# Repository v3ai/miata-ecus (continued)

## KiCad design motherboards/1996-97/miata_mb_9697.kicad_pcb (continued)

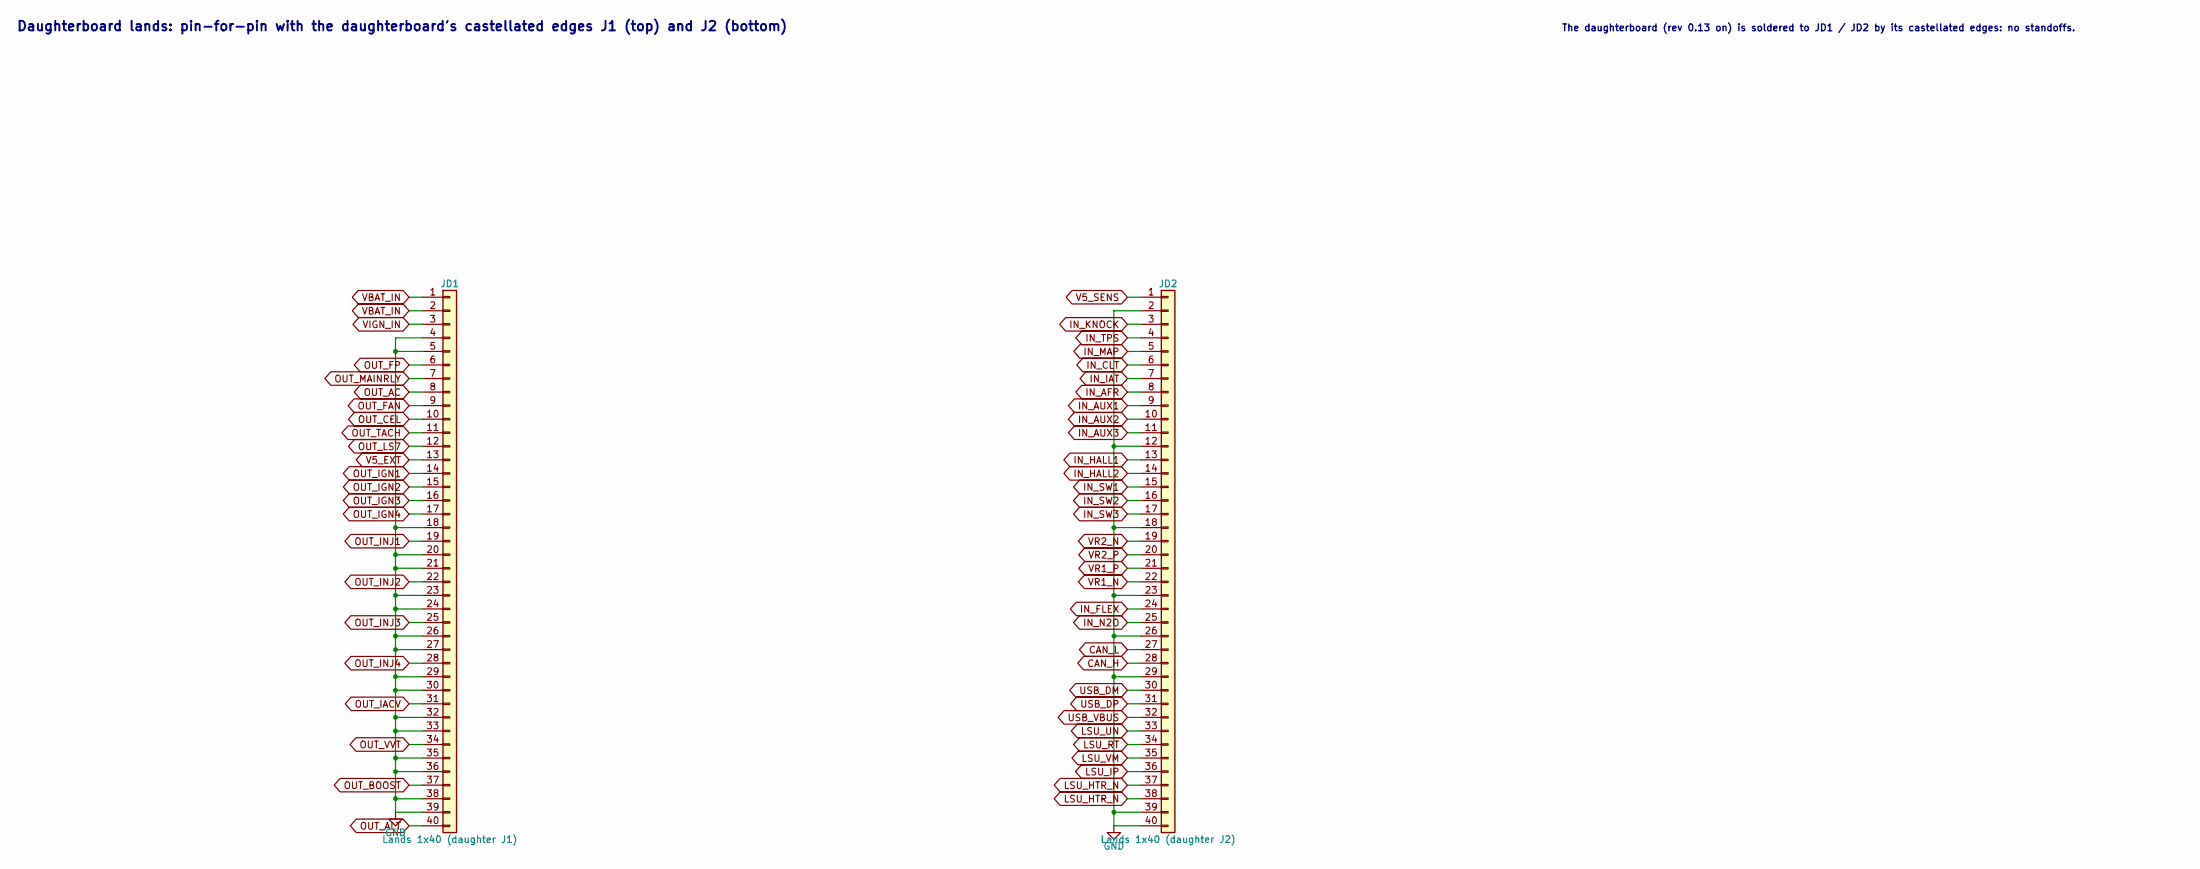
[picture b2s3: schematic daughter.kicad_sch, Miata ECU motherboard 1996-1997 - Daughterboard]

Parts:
JD1: Lands 1x40 (daughter J1); CastellatedLand_1x40_P2.54mm_TopEdge
JD2: Lands 1x40 (daughter J2); CastellatedLand_1x40_P2.54mm_BottomEdge

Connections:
CAN_H: JD2.28; also elsewhere on the board
CAN_L: JD2.27; also elsewhere on the board
GND: JD1.4, JD1.5, JD1.18, JD1.20, JD1.21, JD1.23, JD1.24, JD1.26, JD1.27, JD1.29, JD1.30, JD1.32, JD1.33, JD1.35, JD1.36, JD1.38, JD1.39, JD2.2, JD2.12, JD2.18, JD2.23, JD2.26, JD2.29, JD2.39, JD2.40; also elsewhere on the board
IN_AFR: JD2.8; also elsewhere on the board
IN_AUX1: JD2.9; also elsewhere on the board
IN_AUX2: JD2.10; also elsewhere on the board
IN_AUX3: JD2.11; also elsewhere on the board
IN_CLT: JD2.6; also elsewhere on the board
IN_FLEX: JD2.24; also elsewhere on the board
IN_HALL1: JD2.13; also elsewhere on the board
IN_HALL2: JD2.14; also elsewhere on the board
IN_IAT: JD2.7; also elsewhere on the board
IN_KNOCK: JD2.3; also elsewhere on the board
IN_MAP: JD2.5; also elsewhere on the board
IN_N2O: JD2.25; also elsewhere on the board
IN_SW1: JD2.15; also elsewhere on the board
IN_SW2: JD2.16; also elsewhere on the board
IN_SW3: JD2.17; also elsewhere on the board
IN_TPS: JD2.4; also elsewhere on the board
LSU_HTR_N: JD2.37, JD2.38; also elsewhere on the board
LSU_IP: JD2.36; also elsewhere on the board
LSU_RT: JD2.34; also elsewhere on the board
LSU_UN: JD2.33; also elsewhere on the board
LSU_VM: JD2.35; also elsewhere on the board
OUT_AC: JD1.8; also elsewhere on the board
OUT_ALT: JD1.40; also elsewhere on the board
OUT_BOOST: JD1.37; also elsewhere on the board
OUT_CEL: JD1.10; also elsewhere on the board
OUT_FAN: JD1.9; also elsewhere on the board
OUT_FP: JD1.6; also elsewhere on the board
OUT_IACV: JD1.31; also elsewhere on the board
OUT_IGN1: JD1.14; also elsewhere on the board
OUT_IGN2: JD1.15; also elsewhere on the board
OUT_IGN3: JD1.16; also elsewhere on the board
OUT_IGN4: JD1.17; also elsewhere on the board
OUT_INJ1: JD1.19; also elsewhere on the board
OUT_INJ2: JD1.22; also elsewhere on the board
OUT_INJ3: JD1.25; also elsewhere on the board
OUT_INJ4: JD1.28; also elsewhere on the board
OUT_LS7: JD1.12; also elsewhere on the board
OUT_MAINRLY: JD1.7; also elsewhere on the board
OUT_TACH: JD1.11; also elsewhere on the board
OUT_VVT: JD1.34; also elsewhere on the board
USB_DM: JD2.30; also elsewhere on the board
USB_DP: JD2.31; also elsewhere on the board
USB_VBUS: JD2.32; also elsewhere on the board
V5_EXT: JD1.13; also elsewhere on the board
V5_SENS: JD2.1; also elsewhere on the board
VBAT_IN: JD1.1, JD1.2; also elsewhere on the board
VIGN_IN: JD1.3
VR1_N: JD2.22; also elsewhere on the board
VR1_P: JD2.21; also elsewhere on the board
VR2_N: JD2.19; also elsewhere on the board
VR2_P: JD2.20; also elsewhere on the board

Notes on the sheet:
Daughterboard lands: pin-for-pin with the daughterboard's castellated edges J1 (top) and J2 (bottom)
The daughterboard (rev 0.13 on) is soldered to JD1 / JD2 by its castellated edges: no standoffs.

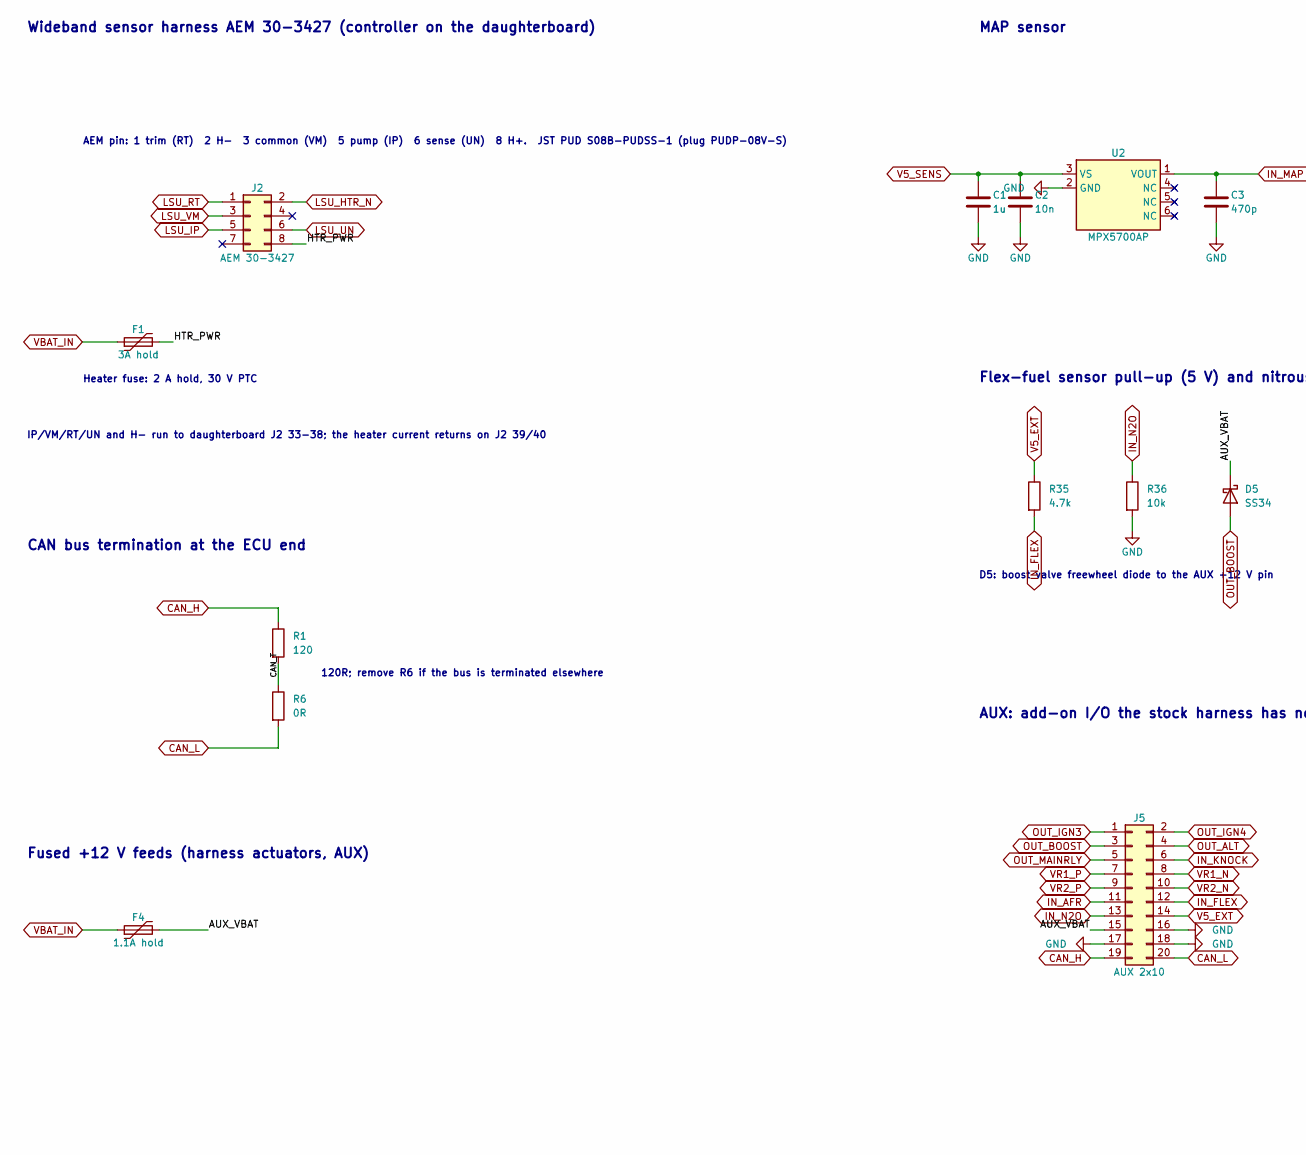
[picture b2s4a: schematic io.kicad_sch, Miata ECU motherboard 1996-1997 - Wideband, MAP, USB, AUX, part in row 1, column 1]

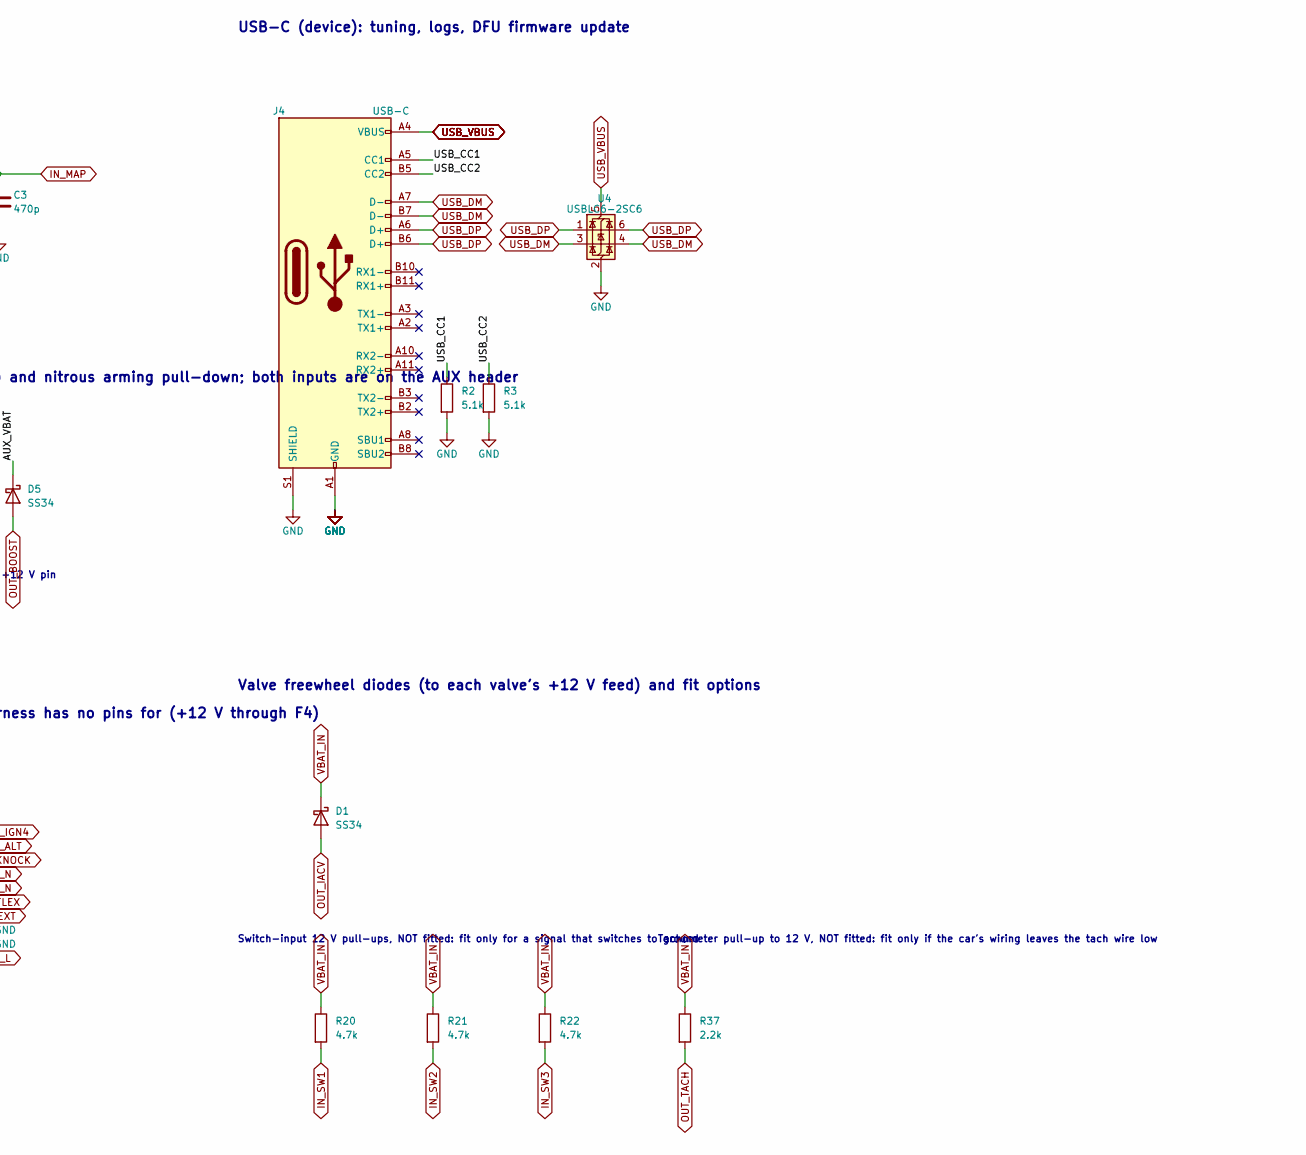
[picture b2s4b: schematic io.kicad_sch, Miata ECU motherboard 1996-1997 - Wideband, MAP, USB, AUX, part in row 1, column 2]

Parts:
C1: 1u; C_0603_1608Metric; LCSC C15849
C2: 10n; C_0603_1608Metric; LCSC C57112
C3: 470p; C_0603_1608Metric; LCSC C1620
D1, D5: SS34; D_SMA; LCSC C8678
F1: 3A hold; Fuse_2920_7451Metric; LCSC C22446884
F4: 1.1A hold; Fuse_1812_4532Metric; LCSC C883150
J2: AEM 30-3427; JST_PUD_S08B-PUDSS-1_2x04_P2.00mm_Horizontal
J4: USB-C; USB_C_GCT_USB4105_16P; LCSC C3020560
J5: AUX 2x10; IDC-Header_2x10_P2.54mm_Vertical
R1: 120; R_0603_1608Metric; LCSC C22787
R2, R3: 5.1k; R_0603_1608Metric; LCSC C23186
R6: 0R; R_0603_1608Metric; LCSC C21189
R20: 4.7k; R_0603_1608Metric
R21, R22, R35: 4.7k; R_0603_1608Metric; LCSC C23162
R36: 10k; R_0603_1608Metric; LCSC C25804
R37: 2.2k; R_1206_3216Metric
U2: MPX5700AP; MPX5700AP_867B_Flat; LCSC C90152
U4: USBLC6-2SC6; SOT-23-6; LCSC C7519

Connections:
/Wideband, MAP, USB, AUX/AUX_VBAT: D5.1 (K), F4.2, J5.15
/Wideband, MAP, USB, AUX/CAN_T: R1.2, R6.1
/Wideband, MAP, USB, AUX/HTR_PWR: F1.2, J2.8
/Wideband, MAP, USB, AUX/USB_CC1: J4.A5 (CC1), R2.1
/Wideband, MAP, USB, AUX/USB_CC2: J4.B5 (CC2), R3.1
CAN_H: J5.19, R1.1; also elsewhere on the board
CAN_L: J5.20, R6.2; also elsewhere on the board
GND: C1.2, C2.2, C3.2, J4.A1 (GND), J4.A12 (GND), J4.B1 (GND), J4.B12 (GND), J4.S1 (SHIELD), J5.16, J5.17, J5.18, R2.2, R3.2, R36.2, U2.2 (GND), U4.2 (GND); also elsewhere on the board
IN_AFR: J5.11; also elsewhere on the board
IN_FLEX: J5.12, R35.2; also elsewhere on the board
IN_KNOCK: J5.6; also elsewhere on the board
IN_MAP: C3.1, U2.1 (VOUT); also elsewhere on the board
IN_N2O: J5.13, R36.1; also elsewhere on the board
IN_SW1: R20.2; also elsewhere on the board
IN_SW2: R21.2; also elsewhere on the board
IN_SW3: R22.2; also elsewhere on the board
LSU_HTR_N: J2.2; also elsewhere on the board
LSU_IP: J2.5; also elsewhere on the board
LSU_RT: J2.1; also elsewhere on the board
LSU_UN: J2.6; also elsewhere on the board
LSU_VM: J2.3; also elsewhere on the board
OUT_ALT: J5.4; also elsewhere on the board
OUT_BOOST: D5.2 (A), J5.3; also elsewhere on the board
OUT_IACV: D1.2 (A); also elsewhere on the board
OUT_IGN3: J5.1; also elsewhere on the board
OUT_IGN4: J5.2; also elsewhere on the board
OUT_MAINRLY: J5.5; also elsewhere on the board
OUT_TACH: R37.2; also elsewhere on the board
USB_DM: J4.A7 (D-), J4.B7 (D-), U4.3 (I/O2), U4.4 (I/O2); also elsewhere on the board
USB_DP: J4.A6 (D+), J4.B6 (D+), U4.1 (I/O1), U4.6 (I/O1); also elsewhere on the board
USB_VBUS: J4.A4 (VBUS), J4.A9 (VBUS), J4.B4 (VBUS), J4.B9 (VBUS), U4.5 (VBUS); also elsewhere on the board
V5_EXT: J5.14, R35.1; also elsewhere on the board
V5_SENS: C1.1, C2.1, U2.3 (VS); also elsewhere on the board
VBAT_IN: D1.1 (K), F1.1, F4.1, R20.1, R21.1, R22.1, R37.1; also elsewhere on the board
VR1_N: J5.8; also elsewhere on the board
VR1_P: J5.7; also elsewhere on the board
VR2_N: J5.10; also elsewhere on the board
VR2_P: J5.9; also elsewhere on the board

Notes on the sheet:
Wideband sensor harness AEM 30-3427 (controller on the daughterboard)
AEM pin: 1 trim (RT) 2 H- 3 common (VM) 5 pump (IP) 6 sense (UN) 8 H+. JST PUD S08B-PUDSS-1 (plug PUDP-08V-S)
IP/VM/RT/UN and H- run to daughterboard J2 33-38; the heater current returns on J2 39/40
Heater fuse: 2 A hold, 30 V PTC
CAN bus termination at the ECU end
120R; remove R6 if the bus is terminated elsewhere
MAP sensor
Flex-fuel sensor pull-up (5 V) and nitrous arming pull-down; both inputs are on the AUX header
D5: boost valve freewheel diode to the AUX +12 V pin
USB-C (device): tuning, logs, DFU firmware update
Fused +12 V feeds (harness actuators, AUX)
AUX: add-on I/O the stock harness has no pins for (+12 V through F4)
Valve freewheel diodes (to each valve's +12 V feed) and fit options
Switch-input 12 V pull-ups, NOT fitted: fit only for a signal that switches to ground
Tachometer pull-up to 12 V, NOT fitted: fit only if the car's wiring leaves the tach wire low

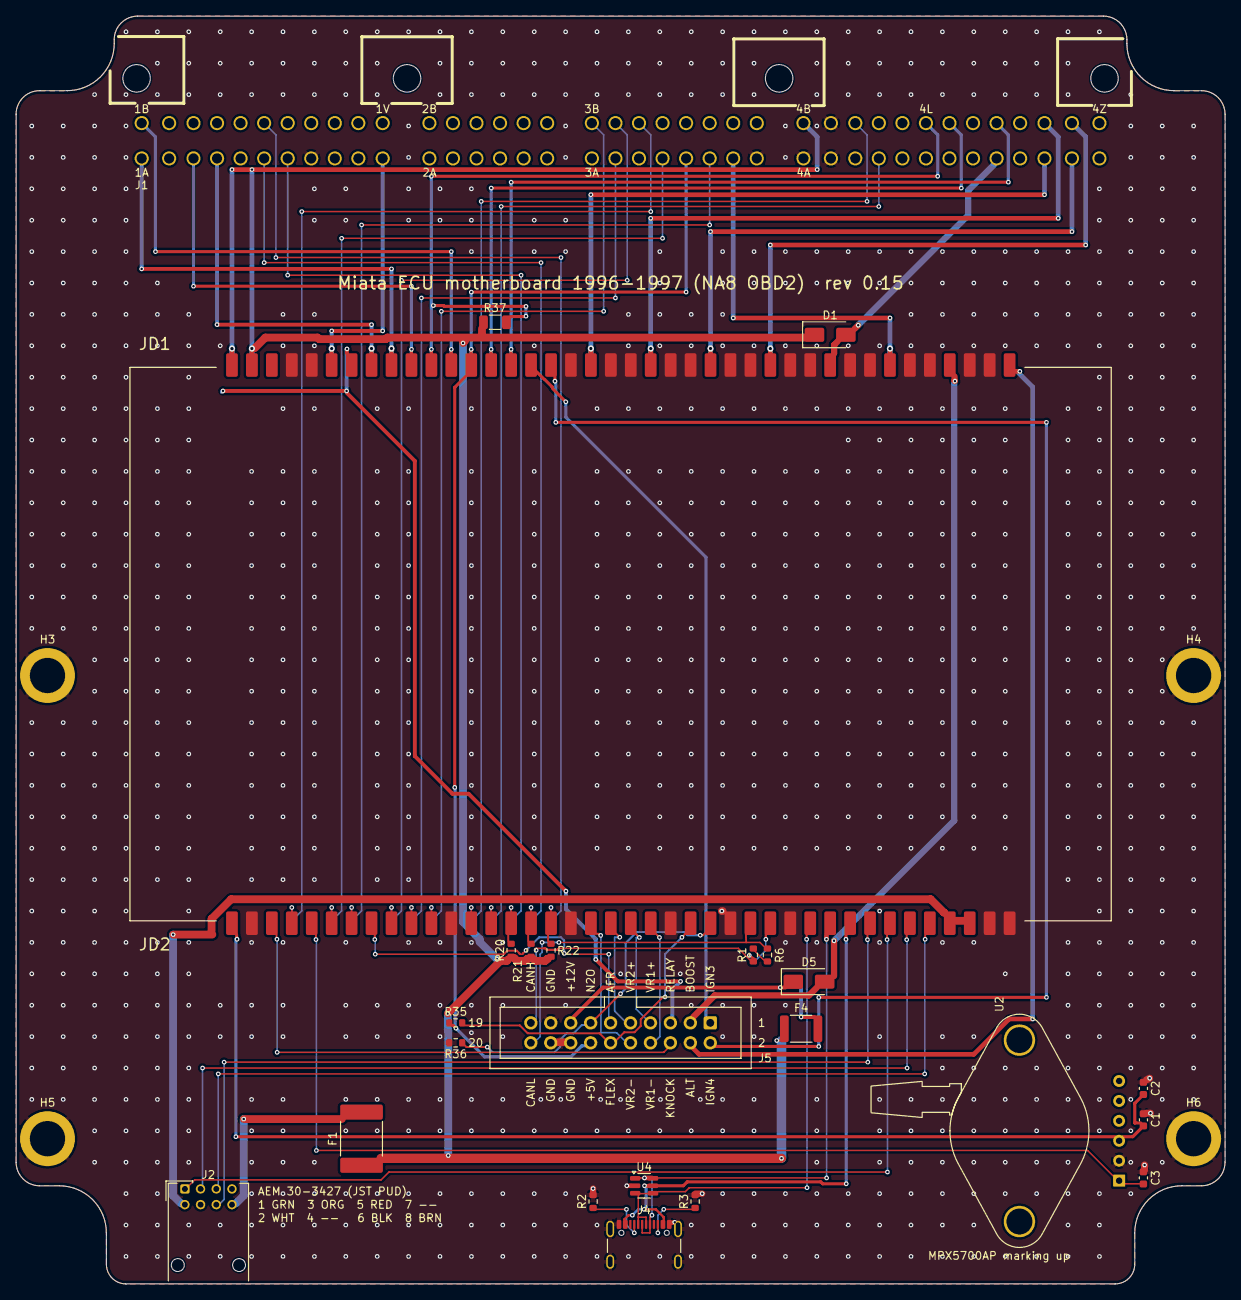
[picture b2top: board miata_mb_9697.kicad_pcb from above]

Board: 2 copper layers, 154.0 x 161.5 mm, 29 parts (0 on the bottom side), 58 nets.

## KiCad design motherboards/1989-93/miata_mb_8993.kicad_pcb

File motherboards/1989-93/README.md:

# Miata ECU motherboard 1989-1993 (NA6), rev 0.11

The motherboard replaces the stock Mazda ECU board inside the **stock ECU case**. It carries:

- the stock harness header;
- the year-independent I/O: the LSU 4.9 wideband sensor connector, IAT, USB-C and the MAP sensor;
- the sockets for the universal daughterboard, which does all the engine control (including the wideband controller).

## Changes in this revision
- Rev 0.11, for daughterboard rev 0.9: the throttle position sensor conversion uses the stock throttle switch plug, as rusEFI's Hellen NA6 and MRE boards do, instead of rev 0.10's separate lead: J6 is gone. Harness pin 1N (the manual cars' idle contact) is no longer wired straight to the sensor 5 V: it goes through R28 (0R, not fitted), so a car with the stock switch no longer shorts the 5 V to ground at every idle (rev 0.10 and earlier did, if 1N is the idle contact as the rusEFI sources say). Pin 2L goes through R29 (0R, fitted) to the spare analog AUX1 as before, or through R30 (0R, not fitted) to the TPS input. For a sensor on the stock plug: fit R28, move R29 to R30. The links are hand-routed into the rev 0.9 copper; nothing else moved.
- Rev 0.10 (replaced by 0.11): J6, a 4-pin connector for a separate TPS lead.
- Rev 0.9, for daughterboard rev 0.9: the daughterboard sits 16 mm lower, centred on the board (42 mm from the top, as up to rev 0.7), with its J1 on its top edge again: JD1 and the upper standoffs HD1/HD2 are back at their rev 0.7 places, JD2, the lower standoffs HD3/HD4, the AUX header J5 (with F4 beside it) and the parts placed against JD2 (CAN termination R1/R6, pull-up options) are 16 mm lower, and the board is routed again. Not compatible with a rev 0.8 daughterboard.
- Rev 0.8, for daughterboard rev 0.8: the harness's sensor 5 V (1N, 2K) and the AUX header pin J5-14 now come from the daughterboard's protected 5 V (V5_EXT, JD1 pin 13, which was a ground pin): a sensor 5 V wire shorted to the battery no longer back-feeds the MAP sensor and the ECU's own 5 V. The MAP sensor keeps its own supply (V5_SENS). The daughterboard outline on the silkscreen is 16 mm taller (125 x 76 mm): its new strip of output drivers overhangs the free area above JD1. D3/D4 (the batch injector clamps) are now SMCJ30A (33.3-36.8 V breakdown) instead of SMCJ40A: the new daughterboard drivers clamp at 40 V minimum, so a 40 V TVS could leave the turn-off energy in a driver; at 30 V the TVS always clamps first. Not-fitted option R27: 4.7k pull-up from the protected 5 V for the manual cars' TPS idle switch on 2L.
- Rev 0.7: LSU heater fuse F1 is a 3 A hold PTC (LUTE 2920L300/30GR, 30 V, 2920 size) instead of the 2 A 1812 part. A cold LSU 4.9 heater draws 1.6-2.3 A rms at the start of the wideband's warm-up, more than the old fuse holds once warm, so it could trip and the controller time out. No 1812 PTC holds 3 A above 8 V.
- Rev 0.6: freewheel diode D1 on the idle valve and D2 on the purge solenoid (2X) to its +12 V feed (the PWM turn-off energy no longer goes into the daughterboard driver); F4 resettable fuse on the AUX +12 V pin J5-15; not-fitted 12 V pull-up options R20-R22 for the VSS / A/C / clutch inputs. INJ1+INJ4 drive 2U and INJ2+INJ3 drive 2V in parallel (R23/R24), with an SMCJ40A clamp per wire (D3/D4), so no driver carries two injectors; 2Y/2Z are only reached through the not-fitted sequential-conversion links R25/R26.
- Rev 0.5: IAT source is now a removable jumper (JP1, 1x3 2.54 mm header + shunt) instead of the R4 / R5 0R links: shunt on EXT (default) reads the IAT connector J3, on STOCK the stock harness sensor; labelled on the silkscreen.
- Rev 0.4: MAP sensor is now the MPX5700AP (absolute, case 867B, one barb; LCSC C90152) instead of the MPX5700DP: new footprint with the real lozenge body and offset barb, holes on the NXP 23.11 mm spacing with 3.3 mm M3 clearance drills.
- Rev 0.3: sensor 5 V now on both 1N (NA6, per the Hellen NA6 map) and 2K; spare low side on 1R (the early cars' BLK/GRN fan-relay wire); 2S left open (it is only used on 94-95).
- Rev 0.2: wideband controller moved to the daughterboard; J5 centred; MAP sensor rotated 90 deg clockwise; LSU connector 6 mm right; SWD header removed; heater fuse now 30 V rated.

## Files
| Path | What |
|---|---|
| `miata_mb_8993.kicad_pro / .kicad_sch / .kicad_pcb` | KiCad 7 project. Root schematic plus three sheets: harness, daughterboard, I/O |
| `miata_mb_8993_schematic.pdf` | Schematic PDF |
| `fab/miata-ecu-motherboard-1989-93-rev0.11_jlcpcb_gerbers.zip`, `fab/miata-ecu-motherboard-1989-93-rev0.11_jlcpcb_bom.csv`, `fab/miata-ecu-motherboard-1989-93-rev0.11_jlcpcb_cpl.csv` | JLC fabrication and assembly files (2 layers, 1.6 mm). The JLC BOM is the SMD parts and USB-C only |
| `fab/miata-ecu-motherboard-1989-93-rev0.11_self_order_bom.csv` | Everything you order and fit yourself: harness header, through-hole connectors, MAP sensor, shunt, standoffs and screws, plus the not-fitted options. Its columns load into LCSC's BOM tool |
| `fab/miata-ecu-motherboard-1989-93-rev0.11_parts_list.csv` | Every part, including the hand-fitted and not-fitted ones |
| `fab/drc_report.txt` | KiCad DRC |
| `ecu_mb.pretty/`, `fp-lib-table` | Project footprints (harness header, MAP sensor lying flat, USB-C, M4 case hole) |
| `renders/` | Top and bottom copper |
| `scripts/` | The design source; `mb_make.sh` rebuilds the whole board |

## Case fit
Stock NA case (same for 1990-95). Outline and holes come from the rusEFI microRusEFI NA plug-and-play board, which fits this case, measured against its known 48-pin header footprint, and from the early Hellen NA6 KiCad board (rev a/b), which uses the same Mazda case outline. H1 is a recessed boss: stack 3 M4 washers under the board.

Board: **154.0 × 161.5 mm**, 1.6 mm. The origin is the top-left corner and y points down, toward the bottom edge.

| Hole | x, y (mm) |
|---|---|
| H1 | 17.0, 7.3 |
| H2 | 137.0, 7.3 |
| H3 | 4.0, 84.0 |
| H4 | 150.0, 84.0 |
| H5 | 4.0, 143.0 |
| H6 | 150.0, 143.0 |

All holes are 4.5 mm plated with a 7 mm pad, tied to GND, for M4 screws. Harness header terminal 1A sits at (39.70, 18.13) mm (lower pin row).

## Harness header
TE **174917-6**, 48 pins: plug 1 = 1A-1V (22 pins), plug 2 = 2A-2Z (26 pins); rusEFI's 1990 page calls the second plug 3A-3Z. TE lists it as not currently available: desolder one from a stock ECU or use a clone. Fitted by hand.

| Pin | Net | Use | Stock function / note |
|---|---|---|---|
| 1B | `VBAT_IN` | ECU power (main relay) | main relay output: ECU power |
| 1C | `VIGN_IN` | switched 12 V sense (wakes the logic supply) | starter (START) signal: battery only while cranking. Not ignition-on: the firmware doesn't use it as ignition sense |
| 1E | `OUT_CEL` | check engine lamp |  |
| 1G | `OUT_IGN1` | ignition 1 (5 V logic) | igniter 1&4 (wasted spark) / COP 1 |
| 1H | `OUT_IGN2` | ignition 2 (5 V logic) | igniter 2&3 (wasted spark) / COP 2 |
| 1J | `OUT_AC` | A/C relay | A/C relay |
| 1L | `OUT_FAN` | fan relay | radiator fan relay |
| 1M | `IN_SW1` | 12 V switch input 1 | vehicle speed sensor |
| 1N | `HARN_1N` |  | manual cars: the stock throttle switch's idle contact (closes to ground at idle). 5 V only through R28 (not fitted), for a 0-5 V sensor on the stock plug |
| 1Q | `IN_SW2` | 12 V switch input 2 | A/C switch |
| 1R | `OUT_LS7` | spare low side | A/C extra cooling fan relay (BLK/GRN) on 1990-91; moved to 1L on later cars |
| 1V | `IN_SW3` | 12 V switch input 3 | clutch switch |
| 2A | `GND` | ground |  |
| 2B | `GND` | ground | power ground |
| 2C | `GND` | ground |  |
| 2D | `GND` | ground | signal ground |
| 2E | `IN_HALL1` | hall input 1 (crank) | CAS crank (SGT, open collector) |
| 2F | `GND` | ground | AFM ground |
| 2G | `IN_HALL2` | hall input 2 (cam) | CAS cam (SGC) |
| 2I | `OUT_TACH` | tach out |  |
| 2K | `V5_EXT` | sensor 5 V reference (out; protected, short-to-battery proof) | 5 V sensor reference (protected harness 5 V) |
| 2L | `HARN_2L` |  | manual cars: the throttle switch's other contact. R29 (fitted) to the spare analog AUX1, or R30 (not fitted) to the TPS input after a sensor conversion |
| 2M | `IN_TPS` | TPS | automatics' TPS signal (a manual car's converted sensor comes in on 2L through R30) |
| 2N | `IN_AUX2` | spare analog 2 | stock narrowband O2 |
| 2O | `IN_AUX3` | spare analog 3 | AFM flap signal |
| 2P | `HARN_IAT` | stock air-temp sensor (JP1 on STOCK) | AFM air temp (IAT jumper JP1 on STOCK to use it) |
| 2Q | `IN_CLT` | coolant temp |  |
| 2T | `OUT_FP` | fuel pump relay | fuel pump relay |
| 2U | `OUT_INJ1` | injector 1 | stock: two injectors on this wire (batch); INJ1 + INJ4 drive it in parallel (R23) |
| 2V | `OUT_INJ2` | injector 2 | stock: the other two injectors (batch); INJ2 + INJ3 in parallel (R24) |
| 2W | `OUT_IACV` | idle air valve |  |
| 2X | `OUT_VVT` | PWM low side (VVT driver) | purge solenoid (VVT driver reused, set as purge / generic PWM) |
| 2Y | `HARN_2Y` |  | empty on manual cars: INJ3 only through R25 (not fitted) after a sequential conversion |
| 2Z | `HARN_2Z` |  | A/T control unit on automatics: INJ4 only through R26 (not fitted), never on an automatic |

Not connected: 1A, 1D, 1F, 1I, 1K, 1O, 1P, 1S, 1T, 1U, 2H, 2J, 2R, 2S.

## Bottom edge, left to right
| Ref | What | Notes |
|---|---|---|
| J2 | LSU 4.9 (Molex Micro-Fit 2×3, right angle) | Pin n = LSU pin n: 1 IP, 2 VM, 3 H−, 4 H+, 5 RT, 6 UN. Heater fed from the main relay through F1 (3 A hold, 30 V, 2920). The controller is on the daughterboard |
| J3 | IAT (Micro-Fit 1×2) | M12×1.5 open-element thermistor, used when the IAT jumper JP1 is on EXT |
| JP1 | IAT source jumper (1×3, 2.54 mm) | Shunt on **2-3 (EXT, default)**: the IAT connector J3. Shunt on **1-2 (STOCK)**: the stock air-temp sensor through the harness (inside the AFM on 1989-97, the MAF on 1999-2005). Set the matching sensor curve in TunerStudio; the pull-up is 2.7 kΩ |
| J4 | USB-C | USB 2.0 device: tuning, logging, DFU |
| U2 | MPX5700AP | Absolute MAP sensor (15-700 kPa, case 867B). Lies flat on 2 × M3, marking side up, leads bent 90° down, the single barb toward the board centre |

**CAN:** R1 + R6 terminate the bus at the ECU end; remove R6 if the bus is terminated elsewhere.

**AUX (J5, 2×8 box header):** what the stock harness has no pins for: COP 3/4, boost, alternator and main-relay outputs, knock input, VR crank/cam inputs, external AFR input, UART, 5 V sensor supply, +12 V and GND.

**Protection (motherboard rev 0.4 / 0.6):** D1 (and D2 where the VVT driver runs a coil) freewheel the PWM valve coils into their own +12 V feed, so the drivers don't absorb the turn-off energy. F4 fuses the AUX +12 V pin (0.5 A hold).

**Switch inputs (R20-R22, not fitted):** the VSS, A/C and clutch inputs read signals that are driven to 12 V. If your car's signal only switches to ground (or is open collector), fit the 4.7 kΩ pull-up for that input. Never fit it for a switch that drives 12 V: the input would always read on.

**Throttle position sensor (manual cars):** the 1989-93 manual cars have no throttle position sensor, only a two-contact switch. The ECU calculates fuel from the MAP sensor, so the car runs without one, but rusEFI then flags the throttle sensor as failed and drops closed-loop idle, throttle-based acceleration fuel and overrun fuel cut. A 0-5 V sensor fits on the stock wiring, as on rusEFI's Hellen NA6 and MRE boards: the switch plug has three wires, the idle contact (1N), ground (2D) and the full-throttle contact (2L), and a sensor needs 5 V, ground and a signal. **Board links:** fit R28 (0R 0805) to put the protected 5 V on 1N, and move the 0R from R29 to R30 so that 2L goes to the TPS input instead of AUX1. Until R28 is fitted, 1N is open: with the stock switch fitted, 5 V on 1N would be shorted to ground at every idle. **Sensor:** a Kia sensor with the same 3-pin Mazda plug (0K01118911 and the others in the self-order BOM) plugs into the stock plug, on a printed mount (Thingiverse 3414132, print in ASA); or Flyin' Miata's TPS upgrade kit. **Before fitting R28,** unplug the switch and check on your car which plug wire reaches 1N, 2L and 2D, and on the sensor which pins are the ends of its track (constant resistance between them at any throttle): those must meet 1N and 2D, and the third (the wiper) 2L. In TunerStudio, calibrate the throttle closed and wide open (a reversed sensor calibrates the same way). **Automatics** already have a sensor on 2M (with its 5 V on 2K): leave R28 and R30 off. Every part is in the self-order BOM.

**Throttle switch contact (R27, not fitted):** on the manual cars 2L is one of the throttle switch's contacts, which closes to ground. Fit the 4.7 kΩ pull-up to the protected 5 V only if you keep the stock switch and want the ECU to read it (on AUX1, through R29); never with a sensor on 2L.

**Sensor 5 V:** the harness's 5 V reference and the AUX header pin J5-14 come from the daughterboard's protected 5 V regulator (V5_EXT; it survives a short to the battery or to ground). The MAP sensor has its own supply (V5_SENS), so a damaged sensor wire doesn't take the MAP reading with it.

**Injectors (1989-93):** the stock harness has two injectors on each of 2U and 2V (about 1.8 A per wire). Two daughterboard drivers share each wire through R23 (INJ1 + INJ4 on 2U) and R24 (INJ2 + INJ3 on 2V); rusEFI's batch mode fires each pair together. D3/D4 (SMCJ30A) clamp each wire at about 37 V, below the drivers' own 40 V minimum clamp, so the drivers never take the turn-off energy. For a sequential conversion (new wires to 2Y/2Z), remove R23/R24, fit R25/R26 and switch the firmware to sequential. **Never fit R26 on an automatic: 2Z goes to the A/T control unit.**

## Assembly
- The daughterboard plugs into JD1/JD2 (8.5 mm sockets) on four M3 × 11 mm standoffs.
- Fitted by hand (all in `fab/miata-ecu-motherboard-1989-93-rev0.11_self_order_bom.csv`): the harness header (salvage from a stock ECU or use a clone), the daughterboard sockets JD1/JD2, the LSU and IAT connectors, the AUX header, the JP1 header and its shunt (EXT or STOCK), the MAP sensor, the standoffs, and any not-fitted option links. JLCPCB fits only the SMD parts and USB-C. USB-C has through-hole shell pegs: check in JLC's quote whether that needs Standard PCBA.
- The case needs cut-outs in its bottom edge for the LSU, IAT, USB-C and MAP hose.

## Still to verify
- The case geometry: hole centres and header 1A position, with calipers on a stock case.
- Your car's fan wiring: early cars switch the fan relay on 1R, later ones on 1L; both are driven (fan and spare outputs).
- LCSC stock for the extended parts (C124412, C127367, C277684, C587650, C3020560, C410772, C46641168, C3406).
- Harness pins 1N and 2L on a 1989-93 car: with the throttle switch unplugged, which plug wire reaches each (the rusEFI sources give 1N = idle contact, 2D = ground, 2L = full-throttle contact). Do this before fitting R28.
- The TPS conversion on a manual car: the sensor and mount against your throttle body, and the sensor's output across the throttle travel (calibrate closed and wide open in TunerStudio).

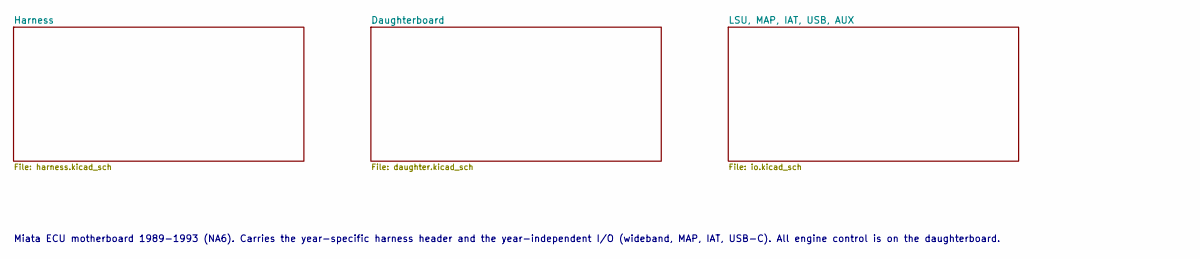
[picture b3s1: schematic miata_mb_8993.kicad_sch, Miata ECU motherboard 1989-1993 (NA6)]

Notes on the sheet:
Miata ECU motherboard 1989-1993 (NA6). Carries the year-specific harness header and the year-independent I/O (wideband, MAP, IAT, USB-C). All engine control is on the daughterboard.

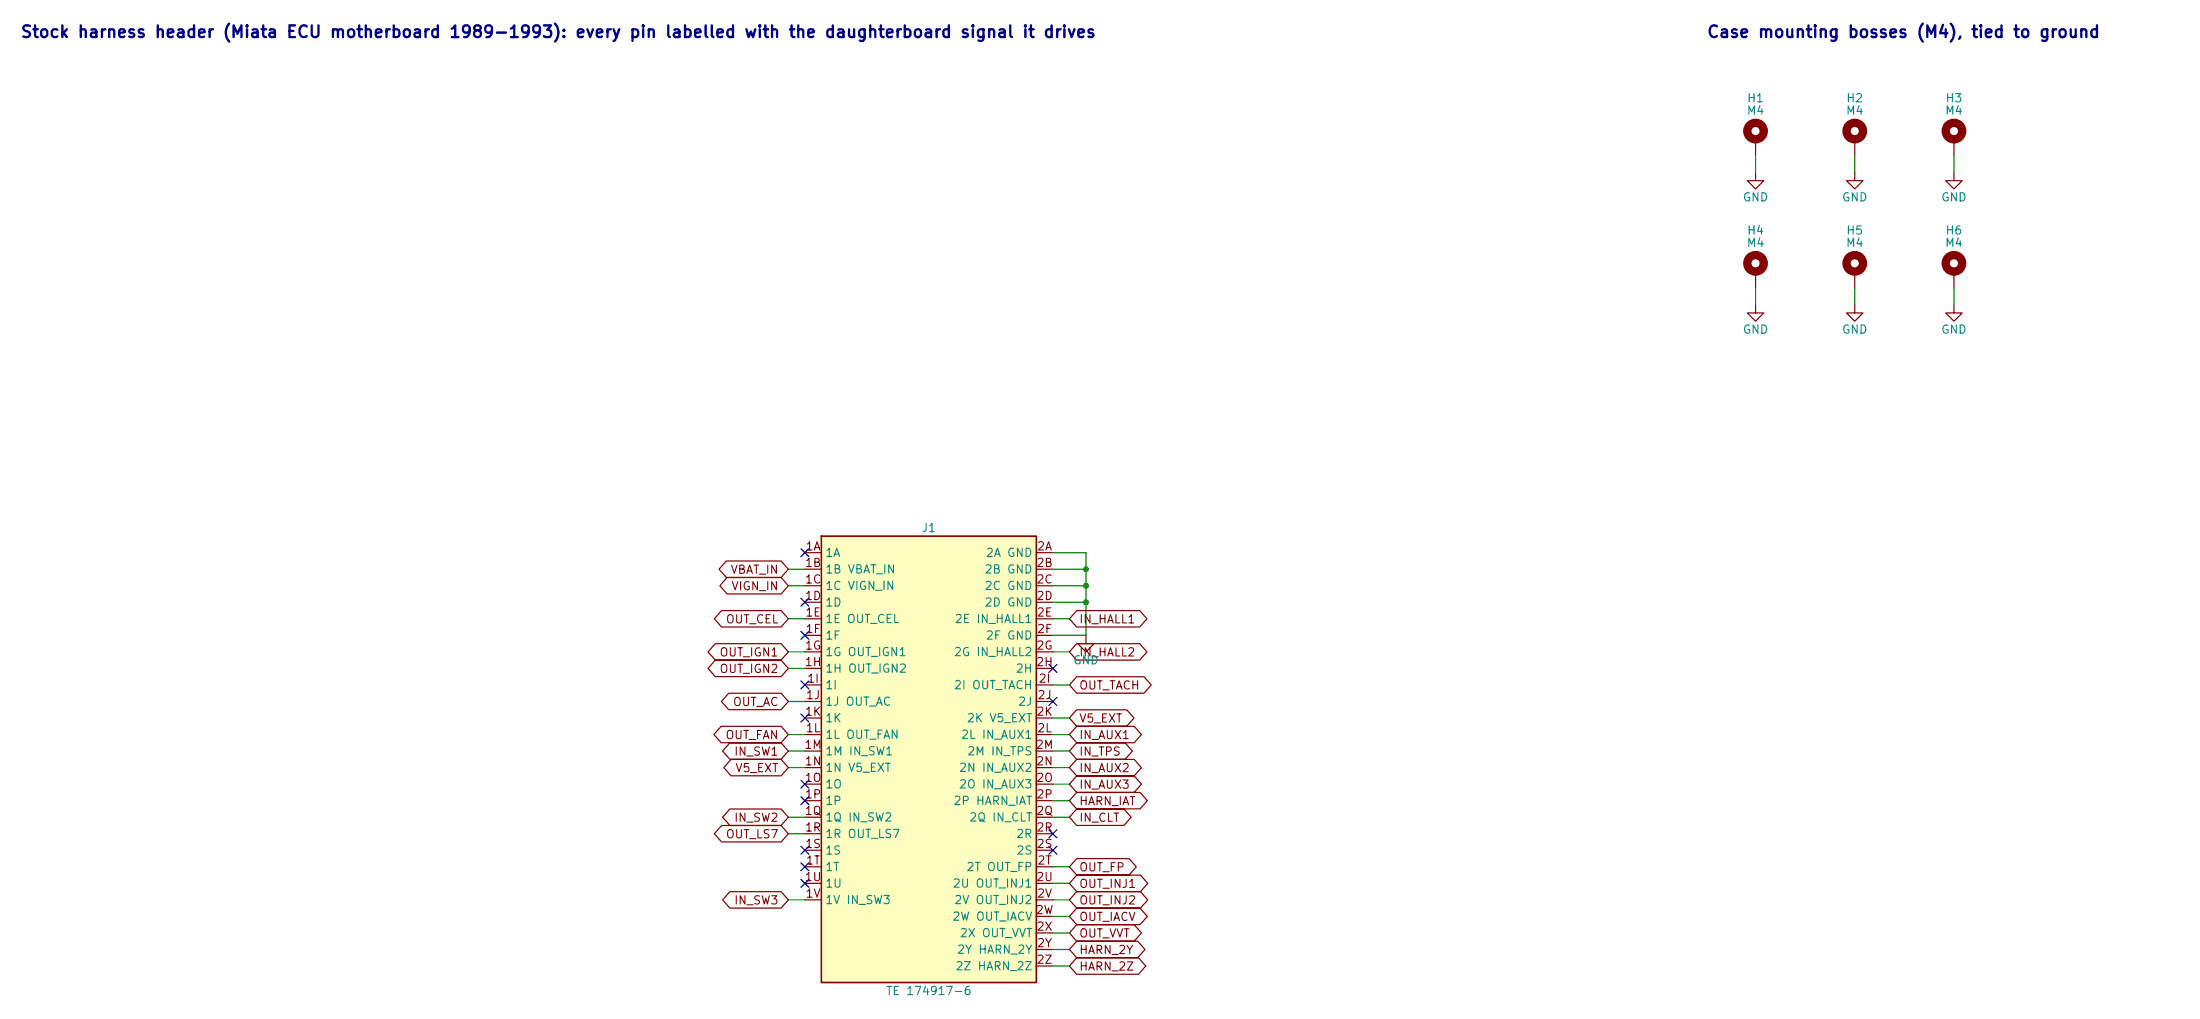
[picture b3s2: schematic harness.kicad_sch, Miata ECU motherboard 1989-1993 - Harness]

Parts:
H1, H2, H3, H4, H5, H6: M4; MountingHole_M4_4.5mm_Pad7
J1: TE 174917-6; TE_174917-6_48P

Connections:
GND: H1.1, H2.1, H3.1, H4.1, H5.1, H6.1, J1.2A (2A GND), J1.2B (2B GND), J1.2C (2C GND), J1.2D (2D GND), J1.2F (2F GND); also elsewhere on the board
HARN_2Y: J1.2Y (2Y HARN_2Y); also elsewhere on the board
HARN_2Z: J1.2Z (2Z HARN_2Z); also elsewhere on the board
HARN_IAT: J1.2P (2P HARN_IAT); also elsewhere on the board
IN_AUX1: J1.2L (2L IN_AUX1); also elsewhere on the board
IN_AUX2: J1.2N (2N IN_AUX2); also elsewhere on the board
IN_AUX3: J1.2O (2O IN_AUX3); also elsewhere on the board
IN_CLT: J1.2Q (2Q IN_CLT); also elsewhere on the board
IN_HALL1: J1.2E (2E IN_HALL1); also elsewhere on the board
IN_HALL2: J1.2G (2G IN_HALL2); also elsewhere on the board
IN_SW1: J1.1M (1M IN_SW1); also elsewhere on the board
IN_SW2: J1.1Q (1Q IN_SW2); also elsewhere on the board
IN_SW3: J1.1V (1V IN_SW3); also elsewhere on the board
IN_TPS: J1.2M (2M IN_TPS); also elsewhere on the board
OUT_AC: J1.1J (1J OUT_AC); also elsewhere on the board
OUT_CEL: J1.1E (1E OUT_CEL); also elsewhere on the board
OUT_FAN: J1.1L (1L OUT_FAN); also elsewhere on the board
OUT_FP: J1.2T (2T OUT_FP); also elsewhere on the board
OUT_IACV: J1.2W (2W OUT_IACV); also elsewhere on the board
OUT_IGN1: J1.1G (1G OUT_IGN1); also elsewhere on the board
OUT_IGN2: J1.1H (1H OUT_IGN2); also elsewhere on the board
OUT_INJ1: J1.2U (2U OUT_INJ1); also elsewhere on the board
OUT_INJ2: J1.2V (2V OUT_INJ2); also elsewhere on the board
OUT_LS7: J1.1R (1R OUT_LS7); also elsewhere on the board
OUT_TACH: J1.2I (2I OUT_TACH); also elsewhere on the board
OUT_VVT: J1.2X (2X OUT_VVT); also elsewhere on the board
V5_EXT: J1.1N (1N V5_EXT), J1.2K (2K V5_EXT); also elsewhere on the board
VBAT_IN: J1.1B (1B VBAT_IN); also elsewhere on the board
VIGN_IN: J1.1C (1C VIGN_IN); also elsewhere on the board

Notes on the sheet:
Stock harness header (Miata ECU motherboard 1989-1993): every pin labelled with the daughterboard signal it drives
Case mounting bosses (M4), tied to ground

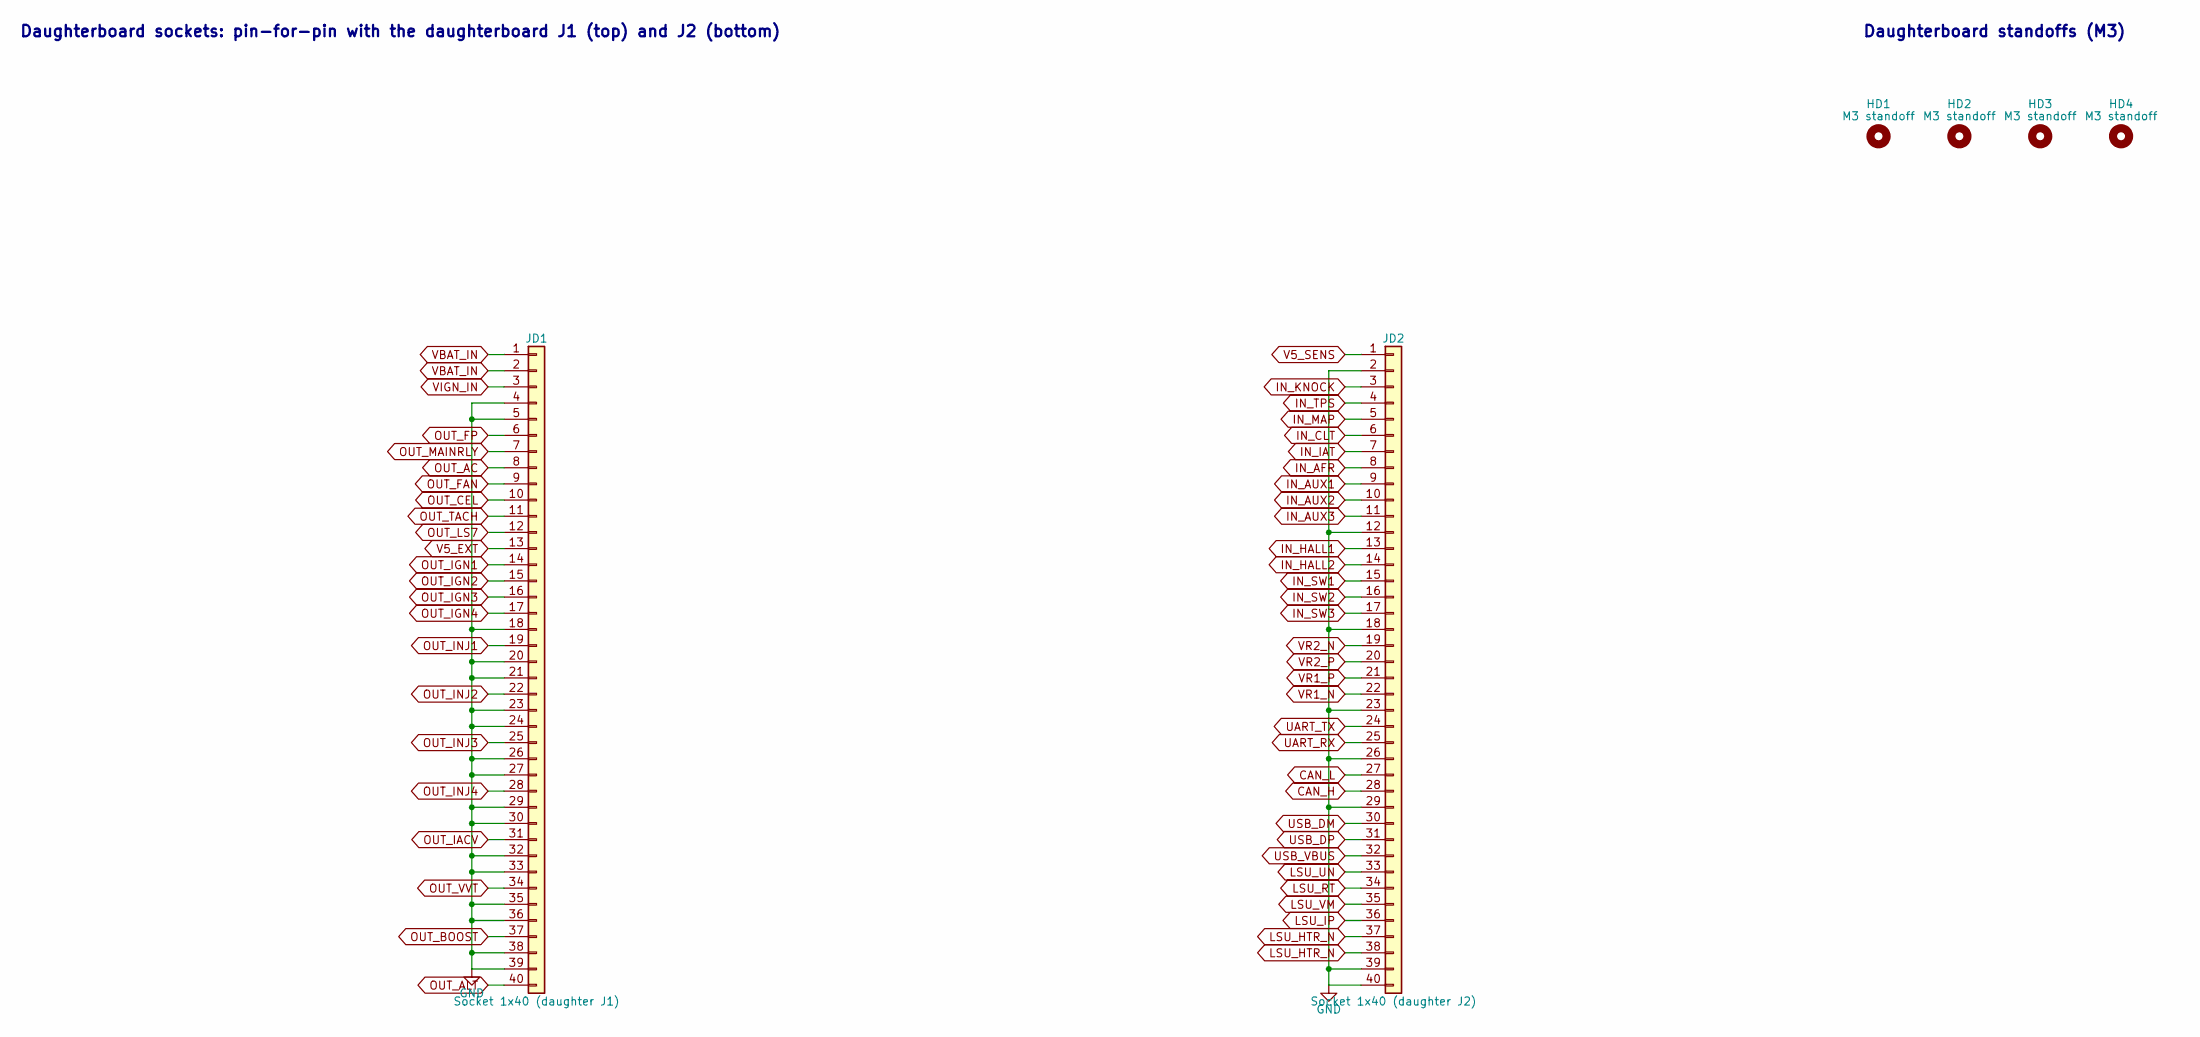
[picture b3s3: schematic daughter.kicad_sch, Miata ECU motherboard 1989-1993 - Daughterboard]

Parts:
HD1, HD2, HD3, HD4: M3 standoff; MountingHole_3.2mm_M3
JD1: Socket 1x40 (daughter J1); PinSocket_1x40_P2.54mm_Vertical; LCSC C124412
JD2: Socket 1x40 (daughter J2); PinSocket_1x40_P2.54mm_Vertical; LCSC C124412

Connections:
CAN_H: JD2.28; also elsewhere on the board
CAN_L: JD2.27; also elsewhere on the board
GND: JD1.4, JD1.5, JD1.18, JD1.20, JD1.21, JD1.23, JD1.24, JD1.26, JD1.27, JD1.29, JD1.30, JD1.32, JD1.33, JD1.35, JD1.36, JD1.38, JD1.39, JD2.2, JD2.12, JD2.18, JD2.23, JD2.26, JD2.29, JD2.39, JD2.40; also elsewhere on the board
IN_AFR: JD2.8; also elsewhere on the board
IN_AUX1: JD2.9; also elsewhere on the board
IN_AUX2: JD2.10; also elsewhere on the board
IN_AUX3: JD2.11; also elsewhere on the board
IN_CLT: JD2.6; also elsewhere on the board
IN_HALL1: JD2.13; also elsewhere on the board
IN_HALL2: JD2.14; also elsewhere on the board
IN_IAT: JD2.7; also elsewhere on the board
IN_KNOCK: JD2.3; also elsewhere on the board
IN_MAP: JD2.5; also elsewhere on the board
IN_SW1: JD2.15; also elsewhere on the board
IN_SW2: JD2.16; also elsewhere on the board
IN_SW3: JD2.17; also elsewhere on the board
IN_TPS: JD2.4; also elsewhere on the board
LSU_HTR_N: JD2.37, JD2.38; also elsewhere on the board
LSU_IP: JD2.36; also elsewhere on the board
LSU_RT: JD2.34; also elsewhere on the board
LSU_UN: JD2.33; also elsewhere on the board
LSU_VM: JD2.35; also elsewhere on the board
OUT_AC: JD1.8; also elsewhere on the board
OUT_ALT: JD1.40; also elsewhere on the board
OUT_BOOST: JD1.37; also elsewhere on the board
OUT_CEL: JD1.10; also elsewhere on the board
OUT_FAN: JD1.9; also elsewhere on the board
OUT_FP: JD1.6; also elsewhere on the board
OUT_IACV: JD1.31; also elsewhere on the board
OUT_IGN1: JD1.14; also elsewhere on the board
OUT_IGN2: JD1.15; also elsewhere on the board
OUT_IGN3: JD1.16; also elsewhere on the board
OUT_IGN4: JD1.17; also elsewhere on the board
OUT_INJ1: JD1.19; also elsewhere on the board
OUT_INJ2: JD1.22; also elsewhere on the board
OUT_INJ3: JD1.25; also elsewhere on the board
OUT_INJ4: JD1.28; also elsewhere on the board
OUT_LS7: JD1.12; also elsewhere on the board
OUT_MAINRLY: JD1.7; also elsewhere on the board
OUT_TACH: JD1.11; also elsewhere on the board
OUT_VVT: JD1.34; also elsewhere on the board
UART_RX: JD2.25; also elsewhere on the board
UART_TX: JD2.24; also elsewhere on the board
USB_DM: JD2.30; also elsewhere on the board
USB_DP: JD2.31; also elsewhere on the board
USB_VBUS: JD2.32; also elsewhere on the board
V5_EXT: JD1.13; also elsewhere on the board
V5_SENS: JD2.1; also elsewhere on the board
VBAT_IN: JD1.1, JD1.2; also elsewhere on the board
VIGN_IN: JD1.3; also elsewhere on the board
VR1_N: JD2.22; also elsewhere on the board
VR1_P: JD2.21; also elsewhere on the board
VR2_N: JD2.19; also elsewhere on the board
VR2_P: JD2.20; also elsewhere on the board

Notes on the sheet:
Daughterboard sockets: pin-for-pin with the daughterboard J1 (top) and J2 (bottom)
Daughterboard standoffs (M3)
